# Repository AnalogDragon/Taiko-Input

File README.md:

# Taiko Input

太鼓输入硬件，usb为HID设备，可以连接2个鼓和8通道的数字量输入。  
文中所提到的太鼓-虹相关的软件，皆下载自互联网。

- [English Version](./README_EN.md)

## [硬件工程](./HW/)
## [USB 单片机](./USB-MCU/)
## [采样单片机](./Sampling-MCU/)
## [上位机](./QT-APP/)
## [文档](./TEXT/)

## 工程结构：
```
|—— HW
    |—— taiko-io
    |—— taiko-io-mini
|—— USB-MCU
    |—— TK_usb_CH552
    |—— TK_usb_CH552_mini
|—— Sampling-MCU
    |—— 8chV3_WithCH552
|—— QT-APP
    |—— APP1_Taiko_IO_Setting
|—— TEXT
```

## HW 硬件工程

硬件工程位于此目录下。  

`taiko-io/`目录内的是双鼓的工程，可用于两个鼓的使用环境（街机），工程使用KICAD设计。  
此项目硬件包含8路模拟输入和8路数字量输入，板载配置接口，单usb供电。  

`taiko-io-mini/`目录内的是单鼓的工程，一般用于一个鼓的使用环境，工程使用LCEDA设计。  
此项目硬件包含4路模拟输入和4个按键，需要测试点配置，单usb供电。  

## USB-MCU USB单片机

USB单片机的软件工程位于此目录下。包含两个软件，根据硬件不同，适配的软件工程也不同。  
使用的单片机为 CH552/CH554，是一款USB 8位单片机。  

`TK_usb_CH552/`目录内的软件适配双鼓硬件（街机），能枚举成为一个USB-HID键盘。  

`TK_usb_CH552_mini/`目录内的软件适配单鼓硬件，可以枚举成不同的USB设备。比如说USB-HID键盘或n******o switch适用的手柄设备。  

软件使用keil 4编译，编译前根据宏可以关闭/打开相关的软件功能。  

## Sampling-MCU 采样单片机

采样单片机的软件工程位于此目录下。软件使用宏区分两款硬件。  
使用的单片机为 STM32G030。  

软件使用keil 5编译，编译前根据宏可以关闭/打开相关的软件功能，切换硬件版本。  

## QT-APP 上位机

上位机的软件工程位于此目录下。上位机可以用于配置硬件的相关参数。  

使用的UI框架为QT 5  

## TEXT 文档

一些中间文档和输出文档位于此目录下。  

# 系统框图
详见[硬件工程](./HW/)  

系统框图  

# 做的一些裂开设计

    主要是通过观察游戏运行的特征，去做体验上的优化。可能合理也可能不合理。

## 游戏软件运行的观察
- 输入频率限制：ns平台的游戏与虹均有输入频率限制。经过测试，每个player独立的。同一个玩家，单个通道限制最高30次每秒，四个通道一起限制60次每秒。超过这个频率的输入会被扔掉。  
也就是说如果只敲左咚或者右咚，则最多30打每秒，而如果左右咚交替输入，能提高到60打每秒。  

- ns平台本身的硬件限制：按键输入会有一个很长的滤波，且按下与松开均需要保持一段时间才能生效。  
在ns游戏内，这个一段时间需要大于20ms。但是主页上则要远大于20ms甚至要到100ms，可能是ns支持可变滤波时间。  

- 虹的数据注入：

## 输出交叉分配

功能实现放在了[USB 单片机](./USB-MCU/)

由于机能或软件运行方式，不同的软件支持的输入最大频率不同，分配输出主要原因是为了能使输入频率达到这台设备的上限。  
表现就是在触发频率高的时候，同一个通道的输入会分配到另一个通道，不同的设备采取的方案不相同。  
- ns：按键消抖做的比较激进，直接在有高频输入的时候，优先分配给同侧的两个按键。
- 虹：游戏软件限制了全局输入的最高频率和单个通道输入的最高频率，可能是为了方便计算图像，这边限制了单一个通道的输入频率，且将同为“咚”的输入分配给空闲的通道。
- PC的其他应用（比如说Open Taiko等）：软件没有做输入频率限制，所以不需要做分配。  

适配虹的交叉分配示意图  

## 信号触发与串音检测

多路信号同时输入的时候，会选择触发幅值更高的通道。  
鼓的传感器被固定在几块相对独立的木板上。通常情况下，直接敲击木板得到的信号，强度是远大于受震动干扰或串扰带来的信号。  

这里的做法是，在首次触发后做微小的延时等待其他通道触发。如果在这期间有多个通道被触发，则输出这里面最强信号的通道。  

触发示意图  

    如果怎么调都会串音，需要考虑是鼓的结构导致的。检查鼓是不是传感器脱落，木板是不是调节的高度不合适等。

# 外观

详见[硬件工程](./HW/) 

## 双鼓硬件（街机/两个鼓场景）

双鼓的硬件3d图  

## 单鼓硬件（自己玩）

单鼓的硬件3d图

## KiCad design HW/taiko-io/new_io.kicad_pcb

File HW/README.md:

# Taiko Input 硬件

Taiko Input 硬件

分为双鼓与单鼓硬件，双鼓设计用于街机或两个鼓的场景，单鼓的硬件则是双鼓硬件简单地切去一半输入前端设计的，在硬件上两者并无很大的差异。

[English Version](./README_EN.md)  

[主页](../)  

## 硬件结构

    整体系统分为传感器（鼓）、前端、采样、USB、PC，其中前端、采样、USB三部分位于input硬件上。
    除此之外还，有电源、滤波电路等未在结构图中体现。

硬件结构  

## 前端电路

    前端电路采用了与SIF Board近似的设计，先进行信号的放大与积分，再限制输出。

其中一路前端电路    

信号的波形

由于来自压电传感器的信号带宽高且信号幅值小，不宜直接进行采样。前端电路将输入信号处理成便于采样的信号。  
在示波器截图中，C1(黄色)为传感器输出，C3（红色）为经过前端电路处理后的信号，C2（蓝色）为程序识别后的输出。  

# 硬件

    硬件分为双鼓硬件和单鼓硬件，双鼓硬件为完整版的硬件，可以用于街机环境。  
    单鼓硬件为双鼓硬件删去一半输入电路的硬件，软件上兼容了更多的单人应用场景。  

## 双鼓硬件

[硬件工程](./taiko-io/)  
[原理图](./taiko-io/new_io.pdf)  

双鼓的硬件3d图  

### 接口

- ① 两个单鼓输入的接口，接口定义借鉴了大力鼓（Taiko Force）。
- ② 一个双鼓的输入接口，可以焊接IDC-16P牛角连接器，或者焊接XAD连接器（B16B-XADSS-N）以兼容不同接口的双太鼓。
- ③ 配置USB接口，用于配置采样单片机。
- ④ 太鼓usb接口，插入电脑会枚举成一个USB-HID键盘设备，用于接收太鼓的数据。
- ⑤ service按键输入，焊接XAD连接器或IDC连接器，以连接不同的按键面板。其中16P接口用于自定义的连接，36P用于12亚的IO板接口（B36B-XADSS-N），40P用于更新框体的IO板接口（B40B-XADSS-N）。可以连接最多8个接地始能的按键。
- ⑥ stm32烧录接口和配置串口。
- ⑦ CH552/CH554的boot选择开关。

## 单鼓硬件
[硬件工程](./taiko-io-mini/)  
[原理图](./taiko-io-mini/Taiko_input_x4.pdf)  

单鼓的硬件3d图  

### 接口

- 只能连接一个鼓的4路传感器，接口定义借鉴了大力鼓（Taiko Force）的接口。
- 四个按键用于启动的模式选择和其他按键。

# 装配

## 双鼓硬件

    双鼓硬件不设计外盒，借鉴街机的装配方式为使用螺柱直接装配。

装配尺寸图  

## 单鼓硬件

    单鼓的硬件使用了一款较通用的胶盒，可以较为方便的携带和连接。

装配示意图1  

装配示意图2  

标签

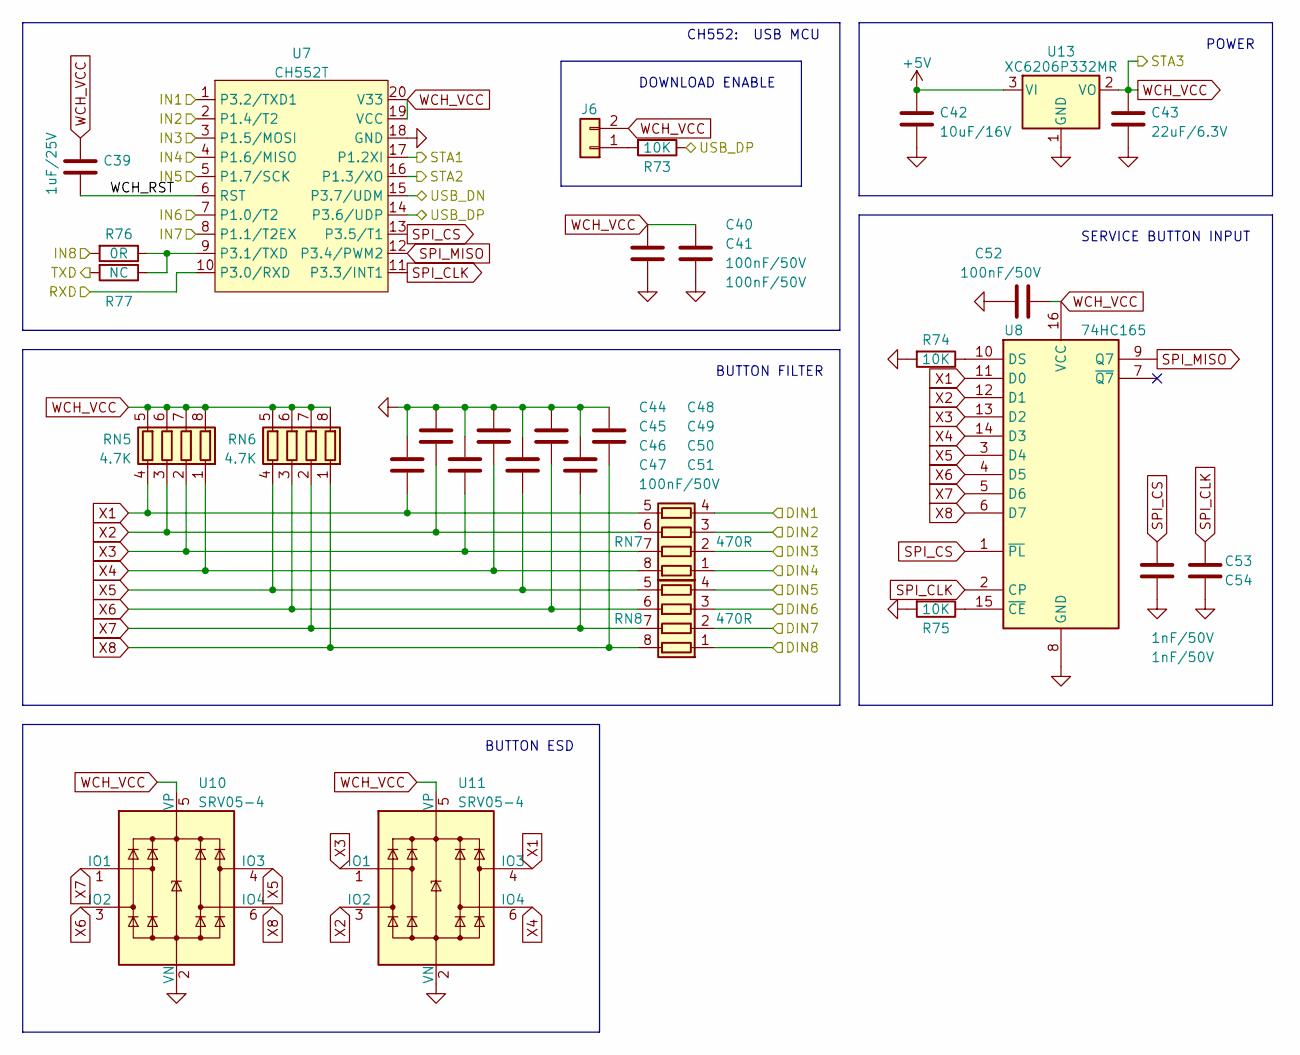
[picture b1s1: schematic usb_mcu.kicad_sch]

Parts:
C39: 1uF/25V; C_0402_1005Metric
C40, C41, C52: 100nF/50V; C_0402_1005Metric
C42: 10uF/16V; C_0603_1608Metric
C43: 22uF/6.3V; C_0603_1608Metric
C44, C45, C46, C47, C48, C49, C50, C51: 100nF/50V; C_0603_1608Metric
C53, C54: 1nF/50V; C_0402_1005Metric
J6: Conn_01x02; PinHeader_1x02_P2.54mm_Vertical
R73, R74, R75: 10K; C_0402_1005Metric
R76: 0R; R_0603_1608Metric
R77: NC; R_0603_1608Metric
RN5, RN6: 4.7K; R_Array_Convex_4x0603
RN7, RN8: 470R; R_Array_Convex_4x0603
U7: CH552T; SSOP-20_4.4x6.5mm_P0.65mm
U8: 74HC165; SOIC-16_3.9x9.9mm_P1.27mm
U10, U11: SRV05-4; SOT-23-6
U13: XC6206P332MR; SOT-23

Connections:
+5V: C42.1, U13.3 (VI); also elsewhere on the board
/interface/DIN1: RN7.4 (R4.1); also elsewhere on the board
/interface/DIN8: RN8.1 (R1.1); also elsewhere on the board
/interface/LED1: U7.1 (P3.2/TXD1); also elsewhere on the board
/interface/LED2: U7.2 (P1.4/T2); also elsewhere on the board
/interface/LED3: U7.3 (P1.5/MOSI); also elsewhere on the board
/interface/LED4: U7.4 (P1.6/MISO); also elsewhere on the board
/interface/LED5: U7.5 (P1.7/SCK); also elsewhere on the board
/interface/LED6: U7.7 (P1.0/T2); also elsewhere on the board
/interface/LED7: U7.8 (P1.1/T2EX); also elsewhere on the board
/interface/LED8: R76.2; also elsewhere on the board
/interface/STA2: U7.17 (P1.2XI); also elsewhere on the board
/interface/STA3: U7.16 (P1.3/XO); also elsewhere on the board
/interface/USB1_DN: U7.15 (P3.7/UDM); also elsewhere on the board
/interface/USB1_DP: R73.1, U7.14 (P3.6/UDP); also elsewhere on the board
/smapling/RXD: R77.2; also elsewhere on the board
/smapling/TXD: U7.10 (P3.0/RXD); also elsewhere on the board
/usb mcu/WCH_RST: C39.2, U7.6 (RST)
unnamed: J6.1, R73.2
unnamed: R76.1, R77.1, U7.9 (P3.1/TXD)
unnamed: R74.1, U8.10 (DS)
unnamed: R75.1, U8.15 (~CE)
SPI_CLK: C54.2, U7.11 (P3.3/INT1), U8.2 (CP)
SPI_CS: C53.2, U7.13 (P3.5/T1), U8.1 (~PL)
SPI_MISO: U7.12 (P3.4/PWM2), U8.9 (Q7)
WCH_VCC: C39.1, C40.1, C41.1, C43.1, C52.2, J6.2, RN5.5 (R4.2), RN5.6 (R3.2), RN5.7 (R2.2), RN5.8 (R1.2), RN6.5 (R4.2), RN6.6 (R3.2), RN6.7 (R2.2), RN6.8 (R1.2), U7.19 (VCC), U7.20 (V33), U8.16 (VCC), U10.5 (VP), U11.5 (VP), U13.2 (VO); also elsewhere on the board
X1: C44.2, RN5.4 (R4.1), RN7.5 (R4.2), U8.11 (D0), U11.4 (IO3)
X2: C45.2, RN5.3 (R3.1), RN7.6 (R3.2), U8.12 (D1), U11.3 (IO2)
X3: C46.2, RN5.2 (R2.1), RN7.7 (R2.2), U8.13 (D2), U11.1 (IO1)
X4: C47.2, RN5.1 (R1.1), RN7.8 (R1.2), U8.14 (D3), U11.6 (IO4)
X5: C48.2, RN6.4 (R4.1), RN8.5 (R4.2), U8.3 (D4), U10.4 (IO3)
X6: C49.2, RN6.3 (R3.1), RN8.6 (R3.2), U8.4 (D5), U10.3 (IO2)
X7: C50.2, RN6.2 (R2.1), RN8.7 (R2.2), U8.5 (D6), U10.1 (IO1)
X8: C51.2, RN6.1 (R1.1), RN8.8 (R1.2), U8.6 (D7), U10.6 (IO4)
coin: RN8.2 (R2.1); also elsewhere on the board
down: RN7.3 (R3.1); also elsewhere on the board
enter: RN8.4 (R4.1); also elsewhere on the board
service: RN7.1 (R1.1); also elsewhere on the board
test: RN8.3 (R3.1); also elsewhere on the board
up: RN7.2 (R2.1); also elsewhere on the board

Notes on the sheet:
SERVICE BUTTON INPUT
DOWNLOAD ENABLE
BUTTON FILTER
POWER
BUTTON ESD
CH552: USB MCU

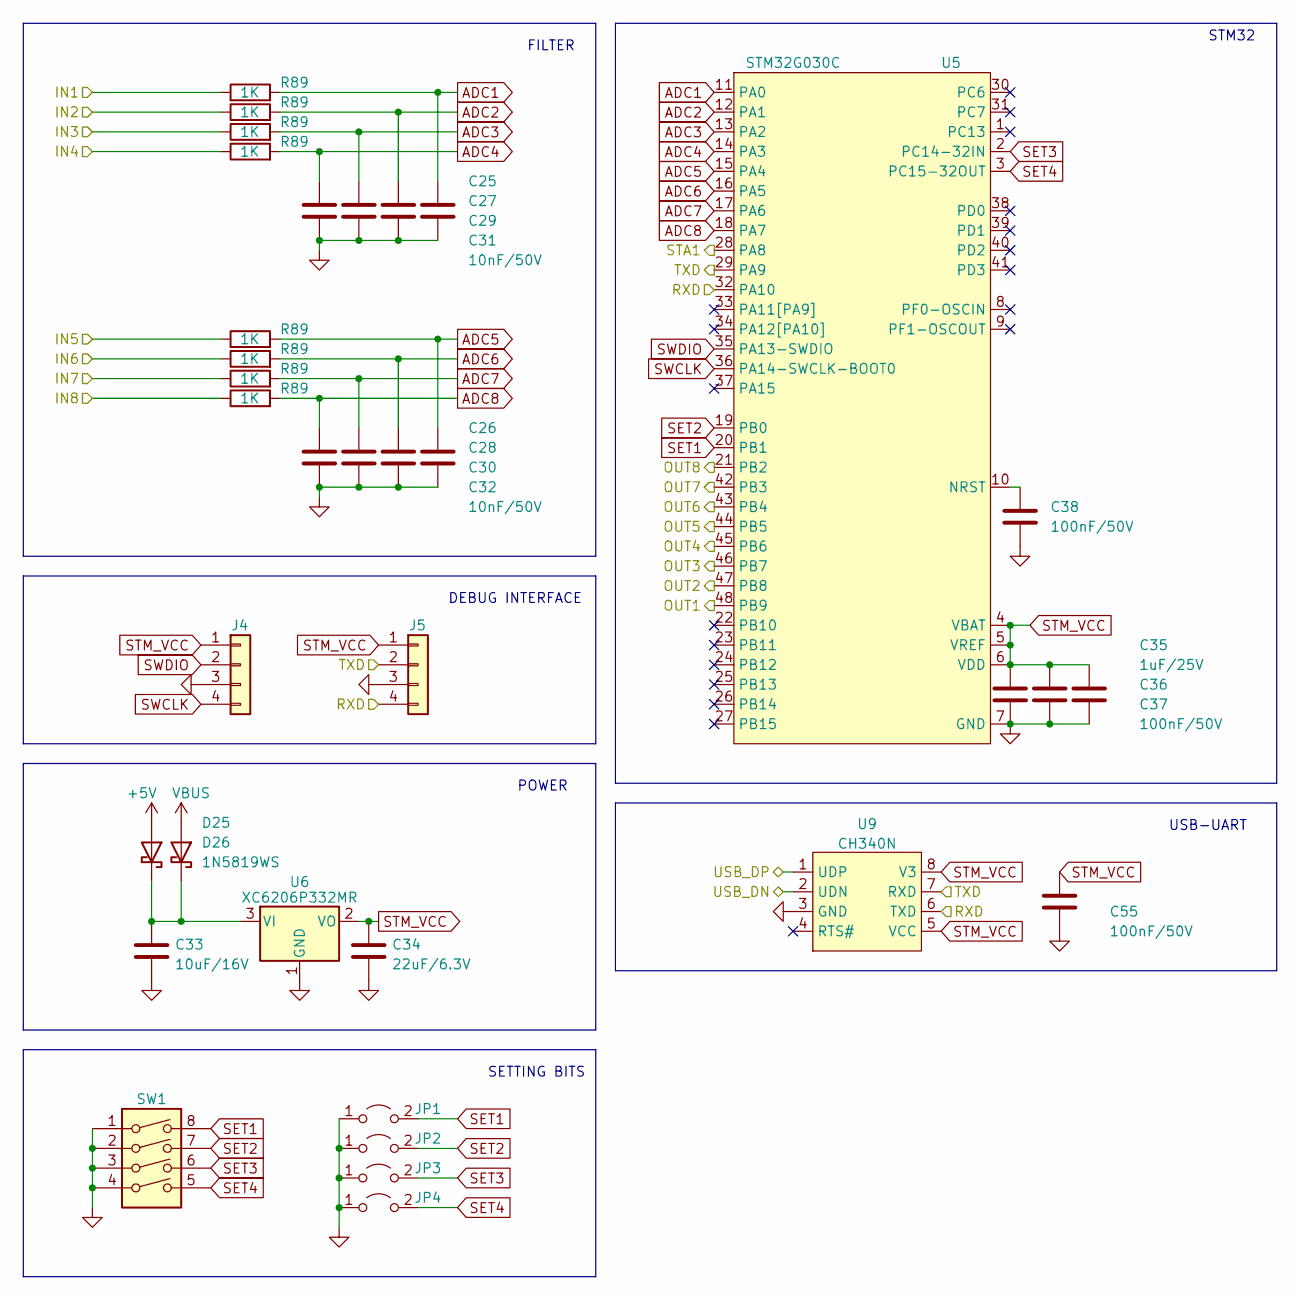
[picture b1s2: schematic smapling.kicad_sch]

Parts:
C25, C26, C27, C28, C29, C30, C31, C32: 10nF/50V; C_0603_1608Metric
C33: 10uF/16V; C_0603_1608Metric
C34: 22uF/6.3V; C_0603_1608Metric
C35: 1uF/25V; C_0402_1005Metric
C36, C37, C38, C55: 100nF/50V; C_0402_1005Metric
D25, D26: 1N5819WS; SOD_323_1
J4, J5: Conn_01x04; PinSocket_1x04_P2.00mm_Vertical
JP1, JP2, JP3, JP4: Jumper_2_Open; JP_0603
R89: 1K; R_0603_1608Metric
SW1: SW_DIP_x04; SW_DIP_SPSTx04_Slide_Copal_CHS-04B_W7.62mm_P1.27mm
U5: STM32G030C; LQFP-48_7x7mm_P0.5mm
U6: XC6206P332MR; SOT-23
U9: CH340N; SOIC-8_3.9x4.9mm_P1.27mm

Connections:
+5V: D25.2 (A); also elsewhere on the board
/frontend/OPA8: R89.1; also elsewhere on the board
/interface/LED1: U5.48 (PB9); also elsewhere on the board
/interface/LED2: U5.47 (PB8); also elsewhere on the board
/interface/LED3: U5.46 (PB7); also elsewhere on the board
/interface/LED4: U5.45 (PB6); also elsewhere on the board
/interface/LED5: U5.44 (PB5); also elsewhere on the board
/interface/LED6: U5.43 (PB4); also elsewhere on the board
/interface/LED7: U5.42 (PB3); also elsewhere on the board
/interface/LED8: U5.21 (PB2); also elsewhere on the board
/interface/STA1: U5.28 (PA8); also elsewhere on the board
/interface/USB2_DN: U9.2 (UDN); also elsewhere on the board
/interface/USB2_DP: U9.1 (UDP); also elsewhere on the board
/smapling/RXD: J5.4, U5.32 (PA10), U9.6 (TXD); also elsewhere on the board
/smapling/TXD: J5.2, U5.29 (PA9), U9.7 (RXD); also elsewhere on the board
unnamed: C33.1, D25.1 (K), D26.1 (K), U6.3 (VI)
unnamed: C38.1, U5.10 (NRST)
SET1: JP1.2 (B), SW1.8, U5.20 (PB1)
SET2: JP2.2 (B), SW1.7, U5.19 (PB0)
SET3: JP3.2 (B), SW1.6, U5.2 (PC14-32IN)
SET4: JP4.2 (B), SW1.5, U5.3 (PC15-32OUT)
STM_VCC: C34.1, C35.1, C36.1, C37.1, C55.1, J4.1, J5.1, U5.4 (VBAT), U5.5 (VREF), U5.6 (VDD), U6.2 (VO), U9.5 (VCC), U9.8 (V3)
SWCLK: J4.4, U5.36 (PA14-SWCLK-BOOT0)
SWDIO: J4.2, U5.35 (PA13-SWDIO)
VBUS: D26.2 (A); also elsewhere on the board

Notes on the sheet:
USB-UART
FILTER
SETTING BITS
DEBUG INTERFACE
STM32
POWER

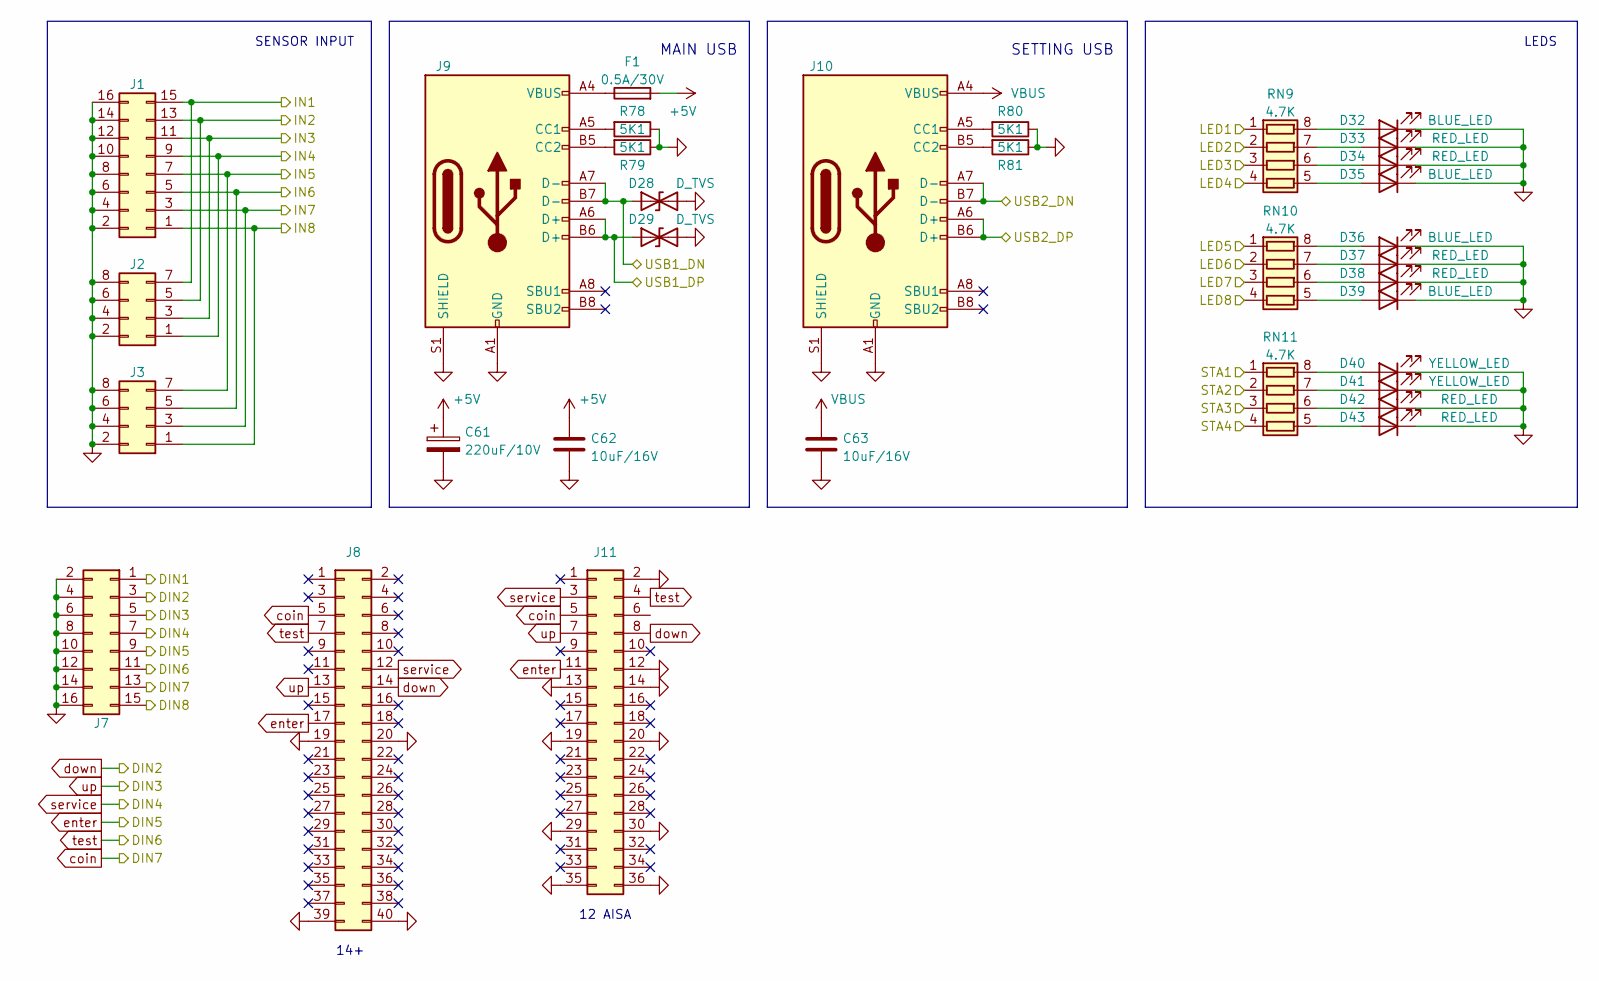
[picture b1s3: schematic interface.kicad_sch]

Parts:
C61: 220uF/10V; CP_Radial_D6.3mm_P2.50mm
C62, C63: 10uF/16V; C_0603_1608Metric
D28, D29: D_TVS; SOD_523_1
D32, D35, D36, D39: BLUE_LED; LED_0603_1608Metric
D33, D34, D37, D38, D42, D43: RED_LED; LED_0603_1608Metric
D40, D41: YELLOW_LED; LED_0603_1608Metric
F1: 0.5A/30V; Fuse_0805_2012Metric
J1, J7: Conn_02x08_Odd_Even; IDC-Header_2x08-1MP_P2.54mm_Latch6.5mm_Vertical
J2, J3: Conn_02x04_Odd_Even; IDC-Header_2x04_P2.54mm_Vertical
J8: Conn_02x20_Odd_Even; B40B-XADSS-N-A
J9, J10: USB_C_Receptacle_USB2.0; USB_C_Receptacle_HRO_TYPE-C-31-M-12
J11: Conn_02x18_Odd_Even; B36B-XADSS-N-A
R78, R79, R80, R81: 5K1; R_0603_1608Metric
RN9, RN10, RN11: 4.7K; R_Array_Convex_4x0603

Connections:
+5V: C61.1, C62.1, F1.2; also elsewhere on the board
/frontend/IN1: J1.15, J2.7; also elsewhere on the board
/frontend/IN2: J1.13, J2.5; also elsewhere on the board
/frontend/IN3: J1.11, J2.3; also elsewhere on the board
/frontend/IN4: J1.9, J2.1; also elsewhere on the board
/frontend/IN5: J1.7, J3.7; also elsewhere on the board
/frontend/IN6: J1.5, J3.5; also elsewhere on the board
/frontend/IN7: J1.3, J3.3; also elsewhere on the board
/frontend/IN8: J1.1, J3.1; also elsewhere on the board
/interface/DIN1: J7.1; also elsewhere on the board
/interface/DIN8: J7.15; also elsewhere on the board
/interface/LED1: RN9.1 (R1.1); also elsewhere on the board
/interface/LED2: RN9.2 (R2.1); also elsewhere on the board
/interface/LED3: RN9.3 (R3.1); also elsewhere on the board
/interface/LED4: RN9.4 (R4.1); also elsewhere on the board
/interface/LED5: RN10.1 (R1.1); also elsewhere on the board
/interface/LED6: RN10.2 (R2.1); also elsewhere on the board
/interface/LED7: RN10.3 (R3.1); also elsewhere on the board
/interface/LED8: RN10.4 (R4.1); also elsewhere on the board
/interface/STA1: RN11.1 (R1.1); also elsewhere on the board
/interface/STA2: RN11.2 (R2.1); also elsewhere on the board
/interface/STA3: RN11.3 (R3.1); also elsewhere on the board
/interface/USB1_DN: D28.1 (A1), J9.A7 (D-), J9.B7 (D-); also elsewhere on the board
/interface/USB1_DP: D29.1 (A1), J9.A6 (D+), J9.B6 (D+); also elsewhere on the board
/interface/USB2_DN: J10.A7 (D-), J10.B7 (D-); also elsewhere on the board
/interface/USB2_DP: J10.A6 (D+), J10.B6 (D+); also elsewhere on the board
unnamed: D32.2 (A), RN9.8 (R1.2)
unnamed: D33.2 (A), RN9.7 (R2.2)
unnamed: D34.2 (A), RN9.6 (R3.2)
unnamed: D35.2 (A), RN9.5 (R4.2)
unnamed: D36.2 (A), RN10.8 (R1.2)
unnamed: D37.2 (A), RN10.7 (R2.2)
unnamed: D38.2 (A), RN10.6 (R3.2)
unnamed: D39.2 (A), RN10.5 (R4.2)
unnamed: D40.2 (A), RN11.8 (R1.2)
unnamed: D41.2 (A), RN11.7 (R2.2)
unnamed: D42.2 (A), RN11.6 (R3.2)
unnamed: D43.2 (A), RN11.5 (R4.2)
unnamed: F1.1, J9.A4 (VBUS), J9.A9 (VBUS), J9.B4 (VBUS), J9.B9 (VBUS)
unnamed: J9.A5 (CC1), R78.2
unnamed: J9.B5 (CC2), R79.2
unnamed: J10.A5 (CC1), R80.2
unnamed: J10.B5 (CC2), R81.2
VBUS: C63.1, J10.A4 (VBUS), J10.A9 (VBUS), J10.B4 (VBUS), J10.B9 (VBUS); also elsewhere on the board
WCH_VCC: RN11.4 (R4.1); also elsewhere on the board
coin: J7.13, J8.5, J11.5; also elsewhere on the board
down: J7.3, J8.14, J11.8; also elsewhere on the board
enter: J7.9, J8.17, J11.11; also elsewhere on the board
service: J7.7, J8.12, J11.3; also elsewhere on the board
test: J7.11, J8.7, J11.4; also elsewhere on the board
up: J7.5, J8.13, J11.7; also elsewhere on the board

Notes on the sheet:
LEDS
SETTING USB
12 AISA
14+
SENSOR INPUT
MAIN USB

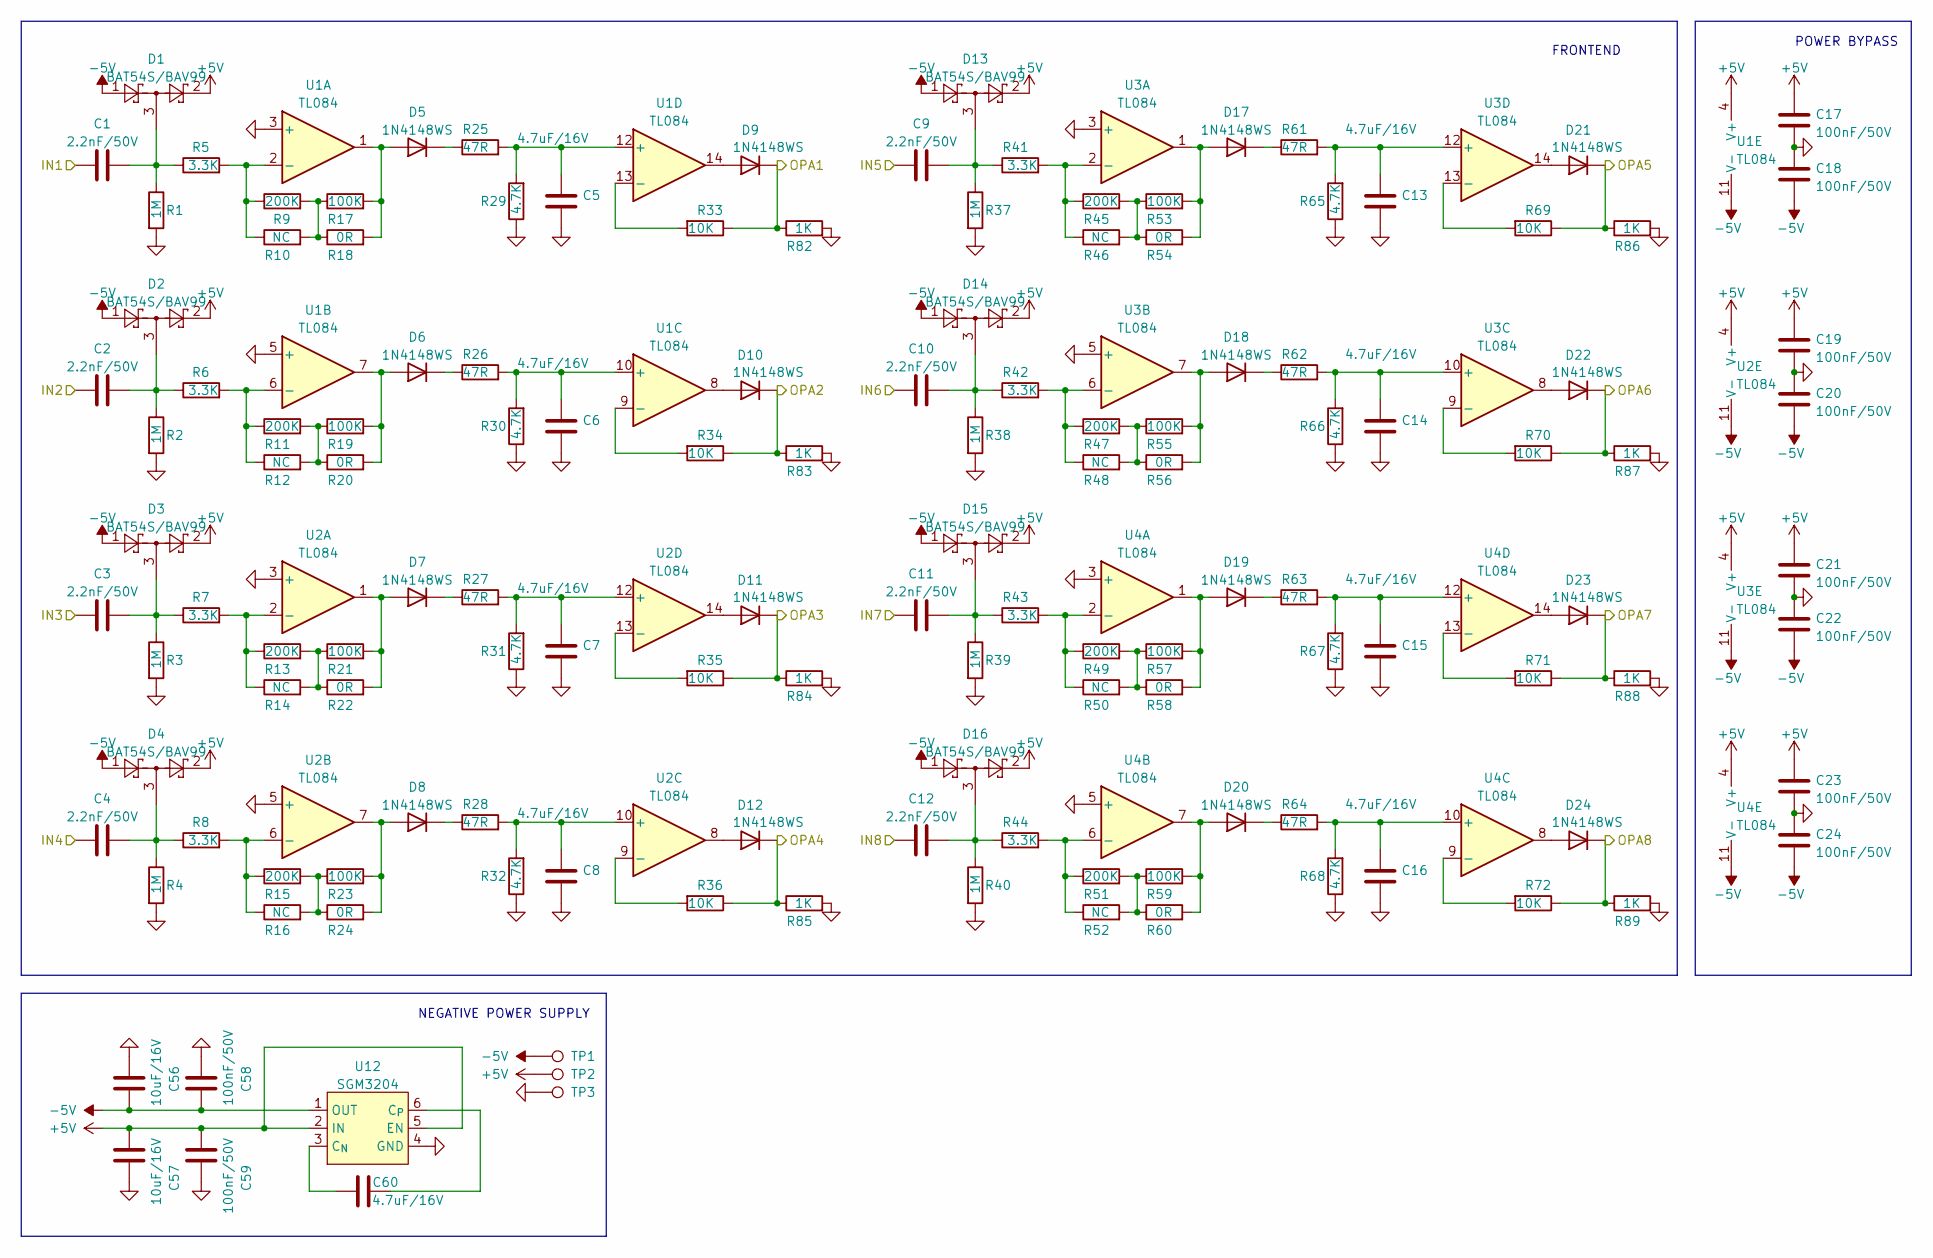
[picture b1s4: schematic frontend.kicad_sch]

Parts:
C1, C2, C3, C4, C9, C10, C11, C12: 2.2nF/50V; C_0603_1608Metric
C5, C6, C7, C8, C13, C14, C15, C16, C60: 4.7uF/16V; C_0603_1608Metric
C17, C18, C19, C20, C21, C22, C23, C24, C58, C59: 100nF/50V; C_0603_1608Metric
C56, C57: 10uF/16V; C_0603_1608Metric
D1, D2, D3, D4, D13, D14, D15, D16: BAT54S/BAV99; SOT-23
D5, D6, D7, D8, D9, D10, D11, D12, D17, D18, D19, D20, D21, D22, D23, D24: 1N4148WS; SOD_323_1
R1, R2, R3, R4, R37, R38, R39, R40: 1M; R_0603_1608Metric
R5, R6, R7, R8, R41, R42, R43, R44: 3.3K; R_0603_1608Metric
R9, R11, R13, R15, R45, R47, R49, R51: 200K; R_0603_1608Metric
R10, R12, R14, R16, R46, R48, R50, R52: NC; R_0603_1608Metric
R17, R19, R21, R23, R53, R55, R57, R59: 100K; R_0603_1608Metric
R18, R20, R22, R24, R54, R56, R58, R60: 0R; R_0603_1608Metric
R25, R26, R27, R28, R61, R62, R63, R64: 47R; R_0603_1608Metric
R29, R30, R31, R32, R65, R66, R67, R68: 4.7K; R_0603_1608Metric
R33, R34, R35, R36, R69, R70, R71, R72: 10K; R_0603_1608Metric
R82, R83, R84, R85, R86, R87, R88, R89: 1K; R_0603_1608Metric
TP1, TP2, TP3: TestPoint; TestPoint_THTPad_D2.0mm_Drill1.0mm
U1, U2, U3, U4: TL084; SOIC-14_3.9x8.7mm_P1.27mm
U12: SGM3204; SOT-23-6

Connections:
+5V: C17.2, C19.2, C21.2, C23.2, C57.1, C59.1, D1.2, D2.2, D3.2, D4.2, D13.2, D14.2, D15.2, D16.2, TP2.1, U1.4 (V+), U2.4 (V+), U3.4 (V+), U4.4 (V+), U12.2 (IN), U12.5 (EN); also elsewhere on the board
-5V: C18.1, C20.1, C22.1, C24.1, C56.2, C58.2, D1.1, D2.1, D3.1, D4.1, D13.1, D14.1, D15.1, D16.1, TP1.1, U1.11 (V-), U2.11 (V-), U3.11 (V-), U4.11 (V-), U12.1 (OUT)
/frontend/IN1: C1.1; also elsewhere on the board
/frontend/IN2: C2.1; also elsewhere on the board
/frontend/IN3: C3.1; also elsewhere on the board
/frontend/IN4: C4.1; also elsewhere on the board
/frontend/IN5: C9.1; also elsewhere on the board
/frontend/IN6: C10.1; also elsewhere on the board
/frontend/IN7: C11.1; also elsewhere on the board
/frontend/IN8: C12.1; also elsewhere on the board
/frontend/OPA1: D9.1 (K), R33.1, R82.1; also elsewhere on the board
/frontend/OPA2: D10.1 (K), R34.1, R83.1; also elsewhere on the board
/frontend/OPA3: D11.1 (K), R35.1, R84.1; also elsewhere on the board
/frontend/OPA4: D12.1 (K), R36.1, R85.1; also elsewhere on the board
/frontend/OPA5: D21.1 (K), R69.1, R86.1; also elsewhere on the board
/frontend/OPA6: D22.1 (K), R70.1, R87.1; also elsewhere on the board
/frontend/OPA7: D23.1 (K), R71.1, R88.1; also elsewhere on the board
/frontend/OPA8: D24.1 (K), R72.1, R89.1; also elsewhere on the board
unnamed: C1.2, D1.3, R1.1, R5.1
unnamed: C2.2, D2.3, R2.1, R6.1
unnamed: C3.2, D3.3, R3.1, R7.1
unnamed: C4.2, D4.3, R4.1, R8.1
unnamed: C9.2, D13.3, R37.1, R41.1
unnamed: C10.2, D14.3, R38.1, R42.1
unnamed: C11.2, D15.3, R39.1, R43.1
unnamed: C12.2, D16.3, R40.1, R44.1
unnamed: D5.2 (A), R17.2, R18.2, U1.1
unnamed: D5.1 (K), R25.1
unnamed: D6.2 (A), R19.2, R20.2, U1.7
unnamed: D6.1 (K), R26.1
unnamed: D7.2 (A), R21.2, R22.2, U2.1
unnamed: D7.1 (K), R27.1
unnamed: D8.2 (A), R23.2, R24.2, U2.7
unnamed: D8.1 (K), R28.1
unnamed: D9.2 (A), U1.14
unnamed: D10.2 (A), U1.8
unnamed: D11.2 (A), U2.14
unnamed: D12.2 (A), U2.8
unnamed: D17.2 (A), R53.2, R54.2, U3.1
unnamed: D17.1 (K), R61.1
unnamed: D18.2 (A), R55.2, R56.2, U3.7
unnamed: D18.1 (K), R62.1
unnamed: D19.2 (A), R57.2, R58.2, U4.1
unnamed: D19.1 (K), R63.1
unnamed: D20.2 (A), R59.2, R60.2, U4.7
unnamed: D20.1 (K), R64.1
unnamed: D21.2 (A), U3.14
unnamed: D22.2 (A), U3.8
unnamed: D23.2 (A), U4.14
unnamed: D24.2 (A), U4.8
unnamed: R9.2, R10.2, R17.1, R18.1
unnamed: R11.2, R12.2, R19.1, R20.1
unnamed: R13.2, R14.2, R21.1, R22.1
unnamed: R15.2, R16.2, R23.1, R24.1
unnamed: R45.2, R46.2, R53.1, R54.1
unnamed: R47.2, R48.2, R55.1, R56.1
unnamed: R49.2, R50.2, R57.1, R58.1
unnamed: R51.2, R52.2, R59.1, R60.1
unnamed: R5.2, R9.1, R10.1, U1.2 (-)
unnamed: R6.2, R11.1, R12.1, U1.6 (-)
unnamed: C6.2, R26.2, R30.2, U1.10 (+)
unnamed: R34.2, U1.9 (-)
unnamed: C5.2, R25.2, R29.2, U1.12 (+)
unnamed: R33.2, U1.13 (-)
unnamed: R7.2, R13.1, R14.1, U2.2 (-)
unnamed: R8.2, R15.1, R16.1, U2.6 (-)
unnamed: C8.2, R28.2, R32.2, U2.10 (+)
unnamed: R36.2, U2.9 (-)
unnamed: C7.2, R27.2, R31.2, U2.12 (+)
unnamed: R35.2, U2.13 (-)
unnamed: R41.2, R45.1, R46.1, U3.2 (-)
unnamed: R42.2, R47.1, R48.1, U3.6 (-)
unnamed: C14.2, R62.2, R66.2, U3.10 (+)
unnamed: R70.2, U3.9 (-)
unnamed: C13.2, R61.2, R65.2, U3.12 (+)
unnamed: R69.2, U3.13 (-)
unnamed: R43.2, R49.1, R50.1, U4.2 (-)
unnamed: R44.2, R51.1, R52.1, U4.6 (-)
unnamed: C16.2, R64.2, R68.2, U4.10 (+)
unnamed: R72.2, U4.9 (-)
unnamed: C15.2, R63.2, R67.2, U4.12 (+)
unnamed: R71.2, U4.13 (-)
unnamed: C60.2, U12.3 (C_{N})
unnamed: C60.1, U12.6 (C_{P})

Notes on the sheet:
FRONTEND
POWER BYPASS
NEGATIVE POWER SUPPLY

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
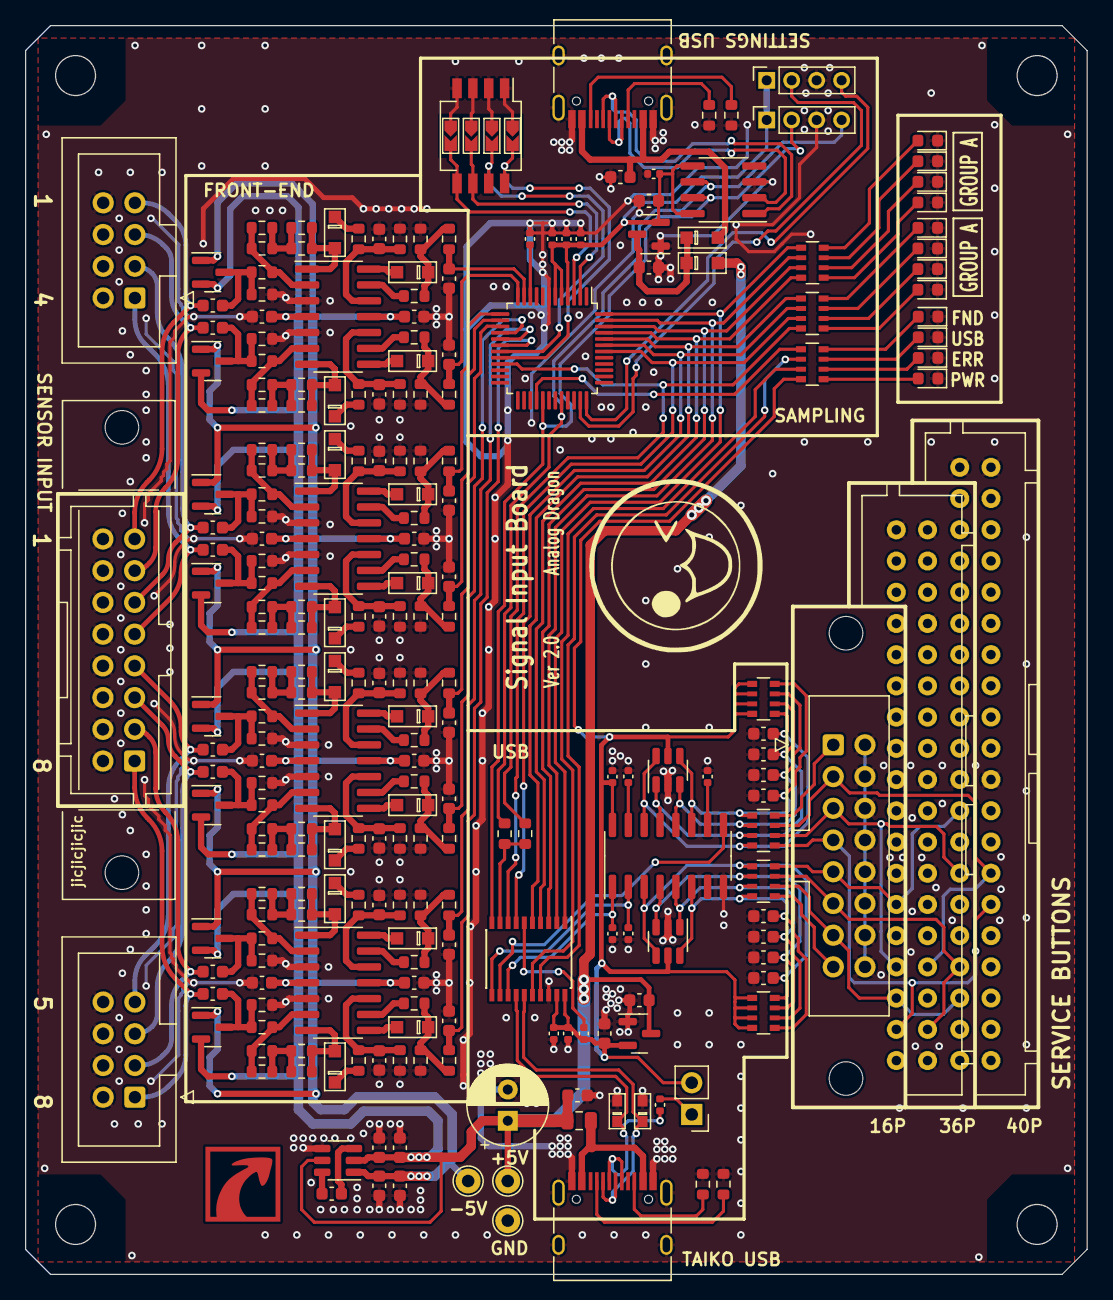
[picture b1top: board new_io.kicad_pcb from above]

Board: 2 copper layers, 85.0 x 100.0 mm, 240 parts (0 on the bottom side), 162 nets.

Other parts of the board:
R90, R91, R92, R93, R94, R95, R96, R97: 1K; R_0603_1608Metric

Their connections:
/frontend/OPA1: R90.1; also elsewhere on the board
/frontend/OPA2: R91.1; also elsewhere on the board
/frontend/OPA3: R92.1; also elsewhere on the board
/frontend/OPA4: R93.1; also elsewhere on the board
/frontend/OPA5: R94.1; also elsewhere on the board
/frontend/OPA6: R95.1; also elsewhere on the board
/frontend/OPA7: R96.1; also elsewhere on the board
/frontend/OPA8: R97.1; also elsewhere on the board

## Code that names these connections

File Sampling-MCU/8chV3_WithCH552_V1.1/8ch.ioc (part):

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Mcu.Name=STM32G030K(6-8)Tx
Mcu.Package=LQFP32
Mcu.UserName=STM32G030K6Tx
PA0.GPIOParameters=GPIO_Label
PA0.GPIO_Label=IN1
PA0.Mode=IN0
PA0.Signal=ADC1_IN0
PA1.GPIOParameters=GPIO_Label
PA1.GPIO_Label=IN2
PA1.Mode=IN1
PA1.Signal=ADC1_IN1
PA10.GPIOParameters=GPIO_PuPd
PA10.GPIO_PuPd=GPIO_PULLUP
PA10.Mode=Asynchronous
PA10.Signal=USART1_RX
PA13.GPIOParameters=GPIO_Label
PA13.GPIO_Label=SWDIO
PA13.Mode=Serial_Wire
PA13.Signal=SYS_SWDIO
PA14-BOOT0.GPIOParameters=GPIO_Label
PA14-BOOT0.GPIO_Label=SWCLK
PA14-BOOT0.Mode=Serial_Wire
PA14-BOOT0.Signal=SYS_SWCLK
PA2.GPIOParameters=GPIO_Label
PA2.GPIO_Label=IN3
PA2.Mode=IN2
PA2.Signal=ADC1_IN2
PA3.GPIOParameters=GPIO_Label
PA3.GPIO_Label=IN4
PA3.Mode=IN3
PA3.Signal=ADC1_IN3
PA4.GPIOParameters=GPIO_Label
PA4.GPIO_Label=IN5
PA4.Mode=IN4
PA4.Signal=ADC1_IN4
PA5.GPIOParameters=GPIO_Label
PA5.GPIO_Label=IN6
PA5.Mode=IN5
PA5.Signal=ADC1_IN5
PA6.GPIOParameters=GPIO_Label
PA6.GPIO_Label=IN7
PA6.Mode=IN6
PA6.Signal=ADC1_IN6
PA7.GPIOParameters=GPIO_Label
PA7.GPIO_Label=IN8
PA7.Mode=IN7
PA7.Signal=ADC1_IN7
PA8.GPIOParameters=GPIO_Label
PA8.GPIO_Label=LED_STA
PA8.Signal=GPIO_Output
PA9.GPIOParameters=GPIO_PuPd
PA9.GPIO_PuPd=GPIO_PULLUP
PA9.Mode=Asynchronous
PA9.Signal=USART1_TX
PB0.GPIOParameters=GPIO_PuPd,GPIO_Label,GPIO_Mode
PB0.GPIO_Label=SET2
PB0.GPIO_Mode=GPIO_MODE_INPUT
PB0.GPIO_PuPd=GPIO_PULLUP
PB0.Signal=GPIO_Input
PB1.GPIOParameters=GPIO_PuPd,GPIO_Label,GPIO_Mode
PB1.GPIO_Label=SET1
PB1.GPIO_Mode=GPIO_MODE_INPUT
PB1.GPIO_PuPd=GPIO_PULLUP
PB1.Signal=GPIO_Input
PB2.GPIOParameters=GPIO_PuPd,GPIO_Label
PB2.GPIO_Label=OUT8
PB2.GPIO_PuPd=GPIO_NOPULL
PB2.Signal=GPIO_Output
PB3.GPIOParameters=GPIO_PuPd,GPIO_Label
PB3.GPIO_Label=OUT7
PB3.GPIO_PuPd=GPIO_NOPULL
PB3.Signal=GPIO_Output
PB4.GPIOParameters=GPIO_PuPd,GPIO_Label
PB4.GPIO_Label=OUT6
PB4.GPIO_PuPd=GPIO_NOPULL
PB4.Signal=GPIO_Output
PB5.GPIOParameters=GPIO_Label
PB5.GPIO_Label=OUT5
PB5.Signal=GPIO_Output
PB6.GPIOParameters=GPIO_Label
PB6.GPIO_Label=OUT4
PB6.Signal=GPIO_Output
PB7.GPIOParameters=GPIO_Label
PB7.GPIO_Label=OUT3
PB7.Signal=GPIO_Output
PB8.GPIOParameters=GPIO_Label
PB8.GPIO_Label=OUT2
PB8.Signal=GPIO_Output
PB9.GPIOParameters=GPIO_Label
PB9.GPIO_Label=OUT1
PB9.Signal=GPIO_Output
PC14-OSC32_IN\ (PC14).GPIOParameters=GPIO_PuPd,GPIO_Label,GPIO_Mode
PC14-OSC32_IN\ (PC14).GPIO_Label=SET3
PC14-OSC32_IN\ (PC14).GPIO_Mode=GPIO_MODE_INPUT
PC14-OSC32_IN\ (PC14).GPIO_PuPd=GPIO_PULLUP
PC14-OSC32_IN\ (PC14).Signal=GPIO_Input
PC15-OSC32_OUT\ (PC15).GPIOParameters=GPIO_PuPd,GPIO_Label,GPIO_Mode
PC15-OSC32_OUT\ (PC15).GPIO_Label=SET4
PC15-OSC32_OUT\ (PC15).GPIO_Mode=GPIO_MODE_INPUT
PC15-OSC32_OUT\ (PC15).GPIO_PuPd=GPIO_PULLUP
PC15-OSC32_OUT\ (PC15).Signal=GPIO_Input
RCC.HSE_VALUE=8000000
RCC.SYSCLKFreq_VALUE=64000000
RCC.SYSCLKSource=RCC_SYSCLKSOURCE_PLLCLK
board=custom

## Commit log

2023-06-22 update md
2023-06-22 update ignore
2023-06-23 Create README_EN.md
    翻译README
2023-06-26 md update
2023-06-28 md ud
2023-07-08 update V201
    增加了mini版本可以關機保存當前啓動模式的功能。
2023-07-28 license
